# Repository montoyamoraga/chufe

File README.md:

# chufe

## About

chufe is an open source hardware Eurorack power supply by [piruetas](https://piruetas.xyz). It takes 12 V DC from a barrel jack, with reverse polarity protection, and outputs ±12V (from a 20 W isolated DC-DC converter) and +5V (from an L7805 linear regulator) on a 16-pin Eurorack power header and a 4-pin Molex KK-396 connector, with an LED for each rail. It is designed to feed a power bus such as [chufebu](https://github.com/piruetasxyz/chufebu). The design is made in KiCad 10 with KiCad's standard libraries plus its own symbol, footprint and 3D model for the DC-DC converter, included in `hardware/bibliotecas/`. Hardware is licensed under CERN-OHL-P-2.0 and documentation under CC-BY-SA-4.0 (see [LICENSE.md](./LICENSE.md)). Documentation, schematic, board render and bill of materials (in Spanish): <https://piruetas.xyz/chufe/>.

## Acerca de

Fuente de alimentación eurorack de [piruetas](https://piruetas.xyz), hecha en KiCad y publicada como hardware de código abierto.

Documentación, esquemático, placa y Bill of materials: <https://piruetas.xyz/chufe/>.

## Características

- Entrada de 12 V DC por jack, con protección contra polaridad inversa.
- Salidas de +12V y -12V desde un convertidor DC-DC aislado de 20 W (URA2412YMD-20WR3).
- Salida de +5V desde un regulador lineal L7805, alimentado desde +12V.
- Un header de alimentación Eurorack de 16 pines (2x08) y un conector Molex KK-396 de 4 pines: -12V, GND, +5V y +12V.
- 4 LEDs indicadores: entrada, -12V, +12V y +5V.
- Placa de 50 × 65 mm, 2 capas, con 4 agujeros de montaje M3.
- Hecha para alimentar un bus como [chufebu](https://github.com/piruetasxyz/chufebu).

## Pines y manual de uso

Los pines del header de 16 pines y del conector KK-396, cómo conectar chufe y las advertencias están en el [manual de uso](https://piruetas.xyz/chufe/#manual-de-uso).

## Revisiones

- `v0.1 rev-a`: fabricada y probada en octubre 2026.

## Estructura del repositorio

- [hardware/chufe-v-0-rev-a](./hardware/chufe-v-0-rev-a): proyecto de KiCad (esquemático y placa), los archivos fuente del diseño.
- [hardware/chufe-v-0-rev-a-fab](./hardware/chufe-v-0-rev-a-fab): gerbers y archivos de taladrado para fabricar la placa.
- [hardware/chufe-v-0-rev-a-pcba](./hardware/chufe-v-0-rev-a-pcba): lista de componentes y archivo de posiciones para armado en JLCPCB.
- [hardware/bibliotecas](./hardware/bibliotecas): símbolo, huella y modelo 3D del convertidor URA2412YMD-20WR3, dibujados por piruetas a partir de la hoja de datos. Van en el repositorio para que el proyecto de KiCad se abra sin instalar bibliotecas adicionales.
- [docs](./docs): documentación, publicada en <https://piruetas.xyz/chufe/>. Las capturas del esquemático y de la placa, y la tabla de Bill of materials, las genera [kicad-retrata](https://github.com/piruetasxyz/kicad-retrata) en cada push (ver [kicad-retrata.yml](./kicad-retrata.yml)).
- [LICENSES](./LICENSES): textos completos de las licencias.

## Fabricación

piruetas vende chufe armado y probado.

Como es hardware de código abierto, los archivos fuente de KiCad, los archivos de fabricación de [hardware/chufe-v-0-rev-a-fab](./hardware/chufe-v-0-rev-a-fab), los de armado de [hardware/chufe-v-0-rev-a-pcba](./hardware/chufe-v-0-rev-a-pcba) y la [Bill of materials](https://piruetas.xyz/chufe/#bill-of-materials-v01-rev-a) están publicados para que cualquiera pueda estudiar, modificar y fabricar el diseño. piruetas no da soporte para unidades fabricadas o armadas por terceros.

## Créditos

- Aarón Montoya-Moraga: investigación, esquemático, PCB, fabricación y documentación.
- Matías Serrano: revisor experto de esquemáticos y PCBs.

## Licencia

chufe es (c) 2026 piruetas SpA / Aarón Montoya-Moraga.

- Hardware (`hardware/`): [CERN-OHL-P-2.0](./LICENSES/CERN-OHL-P-2.0.txt).
- Documentación (`docs/`): [CC-BY-SA-4.0](./LICENSES/CC-BY-SA-4.0.txt).
- El nombre, logo y marca de piruetas no están cubiertos por estas licencias: ver [LicenseRef-piruetas-branding](./LICENSES/LicenseRef-piruetas-branding.txt).

Ver [LICENSE.md](./LICENSE.md) para los detalles. El repositorio sigue la especificación [REUSE](https://reuse.software/).

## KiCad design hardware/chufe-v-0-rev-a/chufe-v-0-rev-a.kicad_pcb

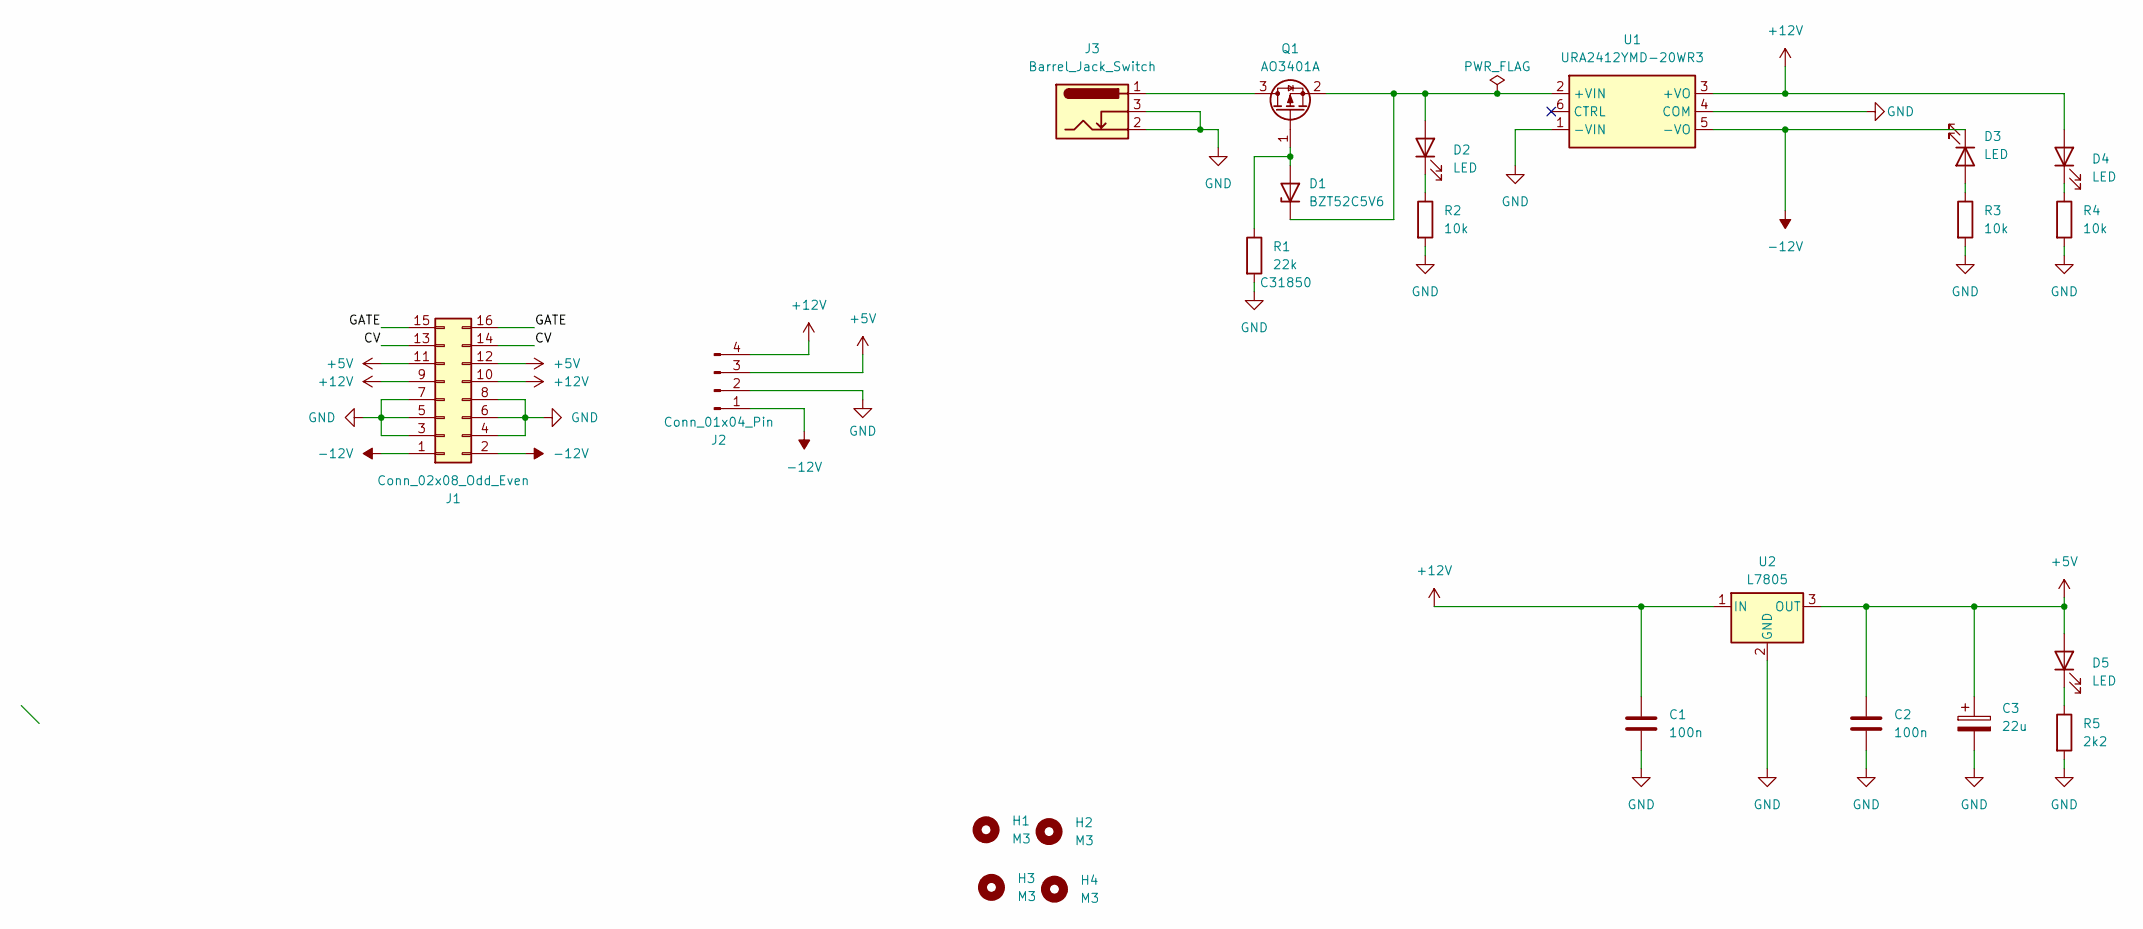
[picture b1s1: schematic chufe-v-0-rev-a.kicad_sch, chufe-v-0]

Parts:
C1, C2: 100n; C_0805_2012Metric; LCSC C49678
C3: 22u; CP_Elec_4x5.4; LCSC C72502
D1: BZT52C5V6; D_SOD-123; LCSC C19077402
D2, D3, D4, D5: LED; LED_D3.0mm
H1, H2, H3, H4: M3; MountingHole_3.2mm_M3
J1: Conn_02x08_Odd_Even; IDC-Header_2x08_P2.54mm_Vertical
J2: Conn_01x04_Pin; Molex_KK-396_5273-04A_1x04_P3.96mm_Vertical
J3: Barrel_Jack_Switch; BarrelJack_Horizontal
Q1: AO3401A; SOT-23; LCSC C15127
R1: 22k; R_0805_2012Metric; LCSC C31850
R2, R3, R4: 10k; R_0805_2012Metric; LCSC C17414
R5: 2k2; R_0805_2012Metric; LCSC C17520
U1: URA2412YMD-20WR3; YLPTEC_URA_YMD-20WR3; MPN URA2412YMD-20WR3; LCSC Part C5369773
U2: L7805; TO-252-2; LCSC C19626525

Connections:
+5V: C2.1, C3.1, D5.2 (A), J1.11, J1.12, J2.3, U2.3 (OUT)
+12V: C1.1, D4.2 (A), J1.9, J1.10, J2.4, U1.3 (+VO), U2.1 (IN)
-12V: D3.1 (K), J1.1, J1.2, J2.1, U1.5 (-VO)
/CV: J1.13, J1.14
/GATE: J1.15, J1.16
GND: C1.2, C2.2, C3.2, J1.3, J1.4, J1.5, J1.6, J1.7, J1.8, J2.2, J3.2, J3.3, R1.2, R2.2, R3.2, R4.2, R5.2, U1.1 (-VIN), U1.4 (COM), U2.2 (GND)
unnamed: D1.2 (A), Q1.1 (G), R1.1
unnamed: D1.1 (K), D2.2 (A), Q1.2 (S), U1.2 (+VIN)
unnamed: D2.1 (K), R2.1
unnamed: D3.2 (A), R3.1
unnamed: D4.1 (K), R4.1
unnamed: D5.1 (K), R5.1
unnamed: J3.1, Q1.3 (D)

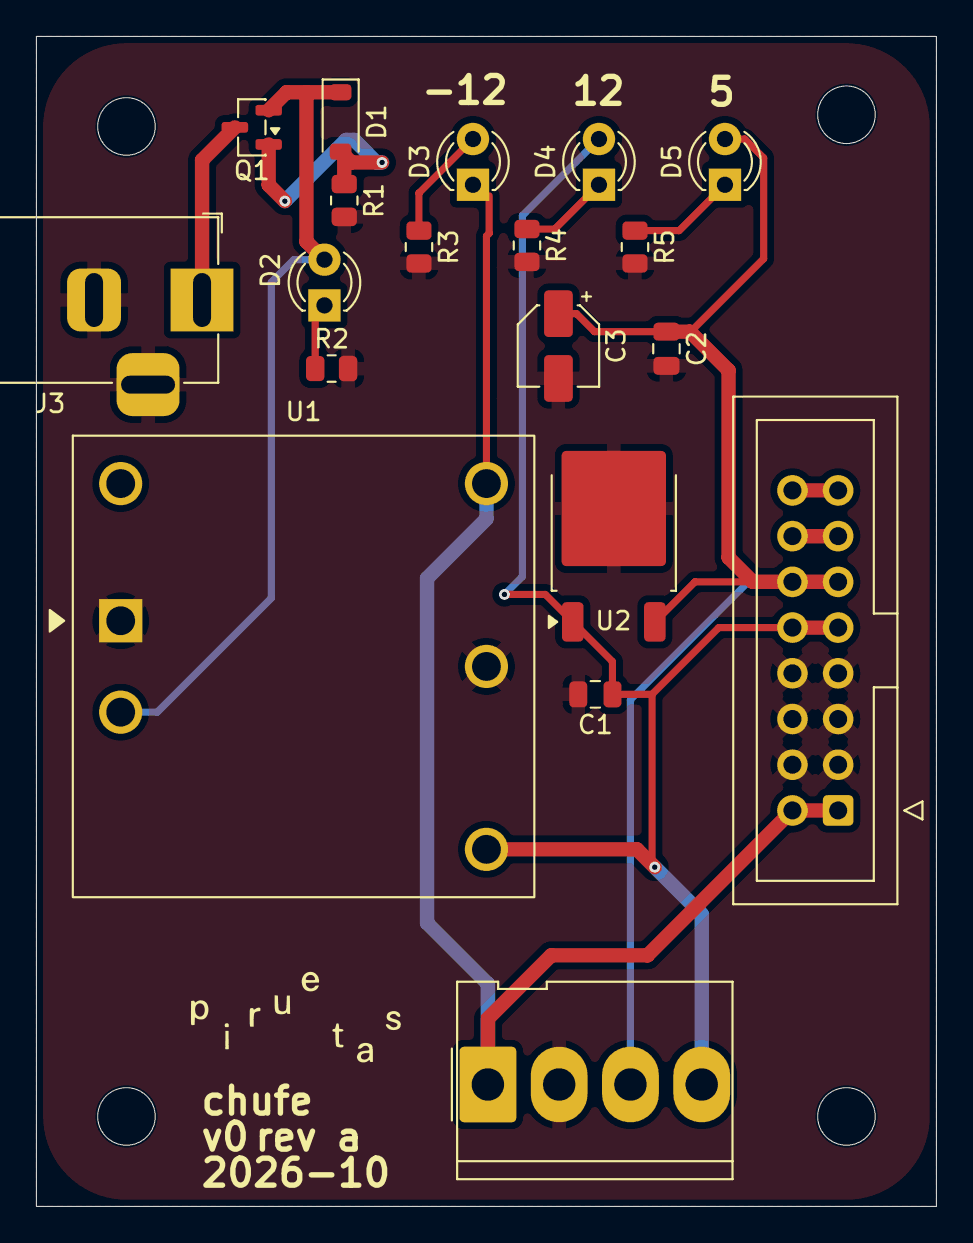
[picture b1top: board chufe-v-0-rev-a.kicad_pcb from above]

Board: 2 copper layers, 50.0 x 65.0 mm, 23 parts (0 on the bottom side), 13 nets.

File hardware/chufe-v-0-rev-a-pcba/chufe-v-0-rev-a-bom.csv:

"Comment","Designator","Footprint","LCSC Part #"
"100n","C1,C2","Capacitor_SMD:C_0805_2012Metric","C49678"
"22u","C3","Capacitor_SMD:CP_Elec_4x5.4","C72502"
"BZT52C5V6","D1","Diode_SMD:D_SOD-123","C19077402"
"AO3401A","Q1","Package_TO_SOT_SMD:SOT-23","C15127"
"22k","R1","Resistor_SMD:R_0805_2012Metric","C31850"
"10k","R2,R3,R4","Resistor_SMD:R_0805_2012Metric","C17414"
"2k2","R5","Resistor_SMD:R_0805_2012Metric","C17520"
"URA2412YMD-20WR3","U1","piruetas:YLPTEC_URA_YMD-20WR3","C5369773"
"L7805","U2","Package_TO_SOT_SMD:TO-252-2","C19626525"
